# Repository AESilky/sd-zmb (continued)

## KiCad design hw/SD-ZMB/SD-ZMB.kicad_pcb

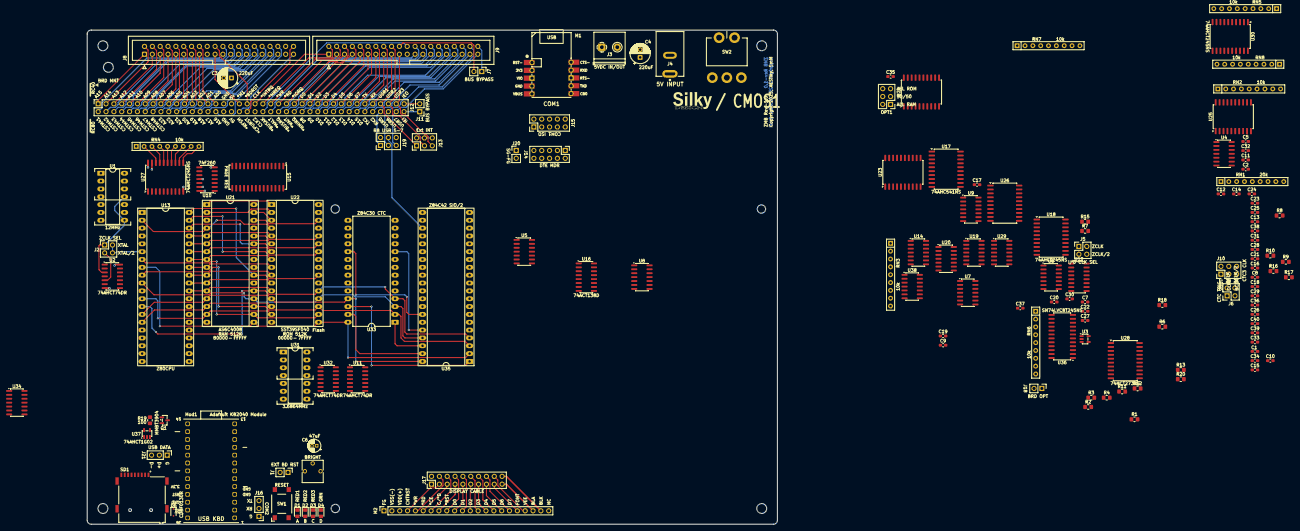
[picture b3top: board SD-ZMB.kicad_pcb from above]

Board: 4 copper layers, 223.5 x 160.0 mm, 147 parts (0 on the bottom side), 263 nets.

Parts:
C1, C2, C5, C7, C8, C9, C10, C11, C12, C13, C14, C15, C16, C17, C18, C19, C20, C21, C22, C23, C24, C25, C26, C27, C28, C29, C30, C31, C32, C33, C34, C35, C36, C37, C38, C39, C40: 0.1uF; C_0603_1608Metric_Pad1.08x0.95mm_HandSolder
C3, C4: 220uF; CP_Radial_D6.3mm_P2.50mm
C6: 47uF; CP_Radial_D4.0mm_P1.50mm
D1, D2, D3: LED RED; LED_0805_2012Metric_Pad1.15x1.40mm_HandSolder
D4: LED GREEN; LED_0805_2012Metric_Pad1.15x1.40mm_HandSolder
D6: CDBF0130R; D_SOD-323F
H1, H2, H3, H4, H8: MountingHole; MountingHole_3.2mm_M3
H5, H6, H7: MountingHole; MountingHole_2.7mm_M2.5
J1, J7, J11, J18, J20: HDR 1x02 Pin; PinHeader_1x02_P2.54mm_Vertical
J2, J5, J6: HDR 02x02; PinHeader_2x02_AB-AES
J3: Screw_Terminal_01x02; AES-TermBlock-2POS-5mm-Horz
J4: BARREL JACK; AES-CUI_PJ-037B
J8, J9: HDR 02x20 PIN (Ribbon Socket); IDC-Header_2x20_P2.54mm_Vertical
J10, J19: Conn_02x03; PinHeader_2x03_AB-AES
J12: SOCKET 02x40 (BRD-CONN); RC80-BUS-BPMB-AES
J13: HDR 02x03 PIN; PinHeader_2x03_AB-AES
J14: CONN 02x05 - DTE_HDR-AES; AES-PinHeader_2x05_DB9-Order
J15: Conn_02x05 HDR; PinHeader_2x05_AB-AES
J16, J21: HDR 1x3 Pin; PinHeader_1x03_P2.54mm_Vertical
J17: HDR 2x10 Pin; PinHeader_2x10_P2.54mm_Vertical
M1: AES-FTDI_FT234XF_USB_UART_Module; AES-FTDI-UMFT234XF
M2: DISPLAY; OLED-Disp-Socket-P2-8BitPI-AES
Mod1: Adafruit KB2040 Module; Adafruit-KB2040-AES
OPT1: HDR 02x03; PinHeader_2x03_AB-AES
Q1: MMBT3904; SOT-23
R1, R2, R3, R4: 510; R_0805_2012Metric_Pad1.20x1.40mm_HandSolder
R6: 10k; R_0805_2012Metric_Pad1.20x1.40mm_HandSolder
R7, R8, R9, R10, R11, R12, R13, R15, R16, R17, R18: 22; R_0805_2012Metric_Pad1.20x1.40mm_HandSolder
R19: 100; R_0805_2012Metric_Pad1.20x1.40mm_HandSolder
R20: 180; R_0805_2012Metric_Pad1.20x1.40mm_HandSolder
RN1: 20k; R_Array_SIP9
RN2, RN3, RN4, RN5, RN6, RN7, RN8: 10k; R_Array_SIP9
RV1: 10k; Pot-Molence-Amazon-PCB-AES
SD1: MicroSD-Socket; AES-SDCard-GCT_MEM2075-00-140-01-A
SW1: SW_Push; AES-SW_PUSH_SMD_1P1T_NO_6x6mm
SW2: SW Toggle PCB; SW-SPDT-PCB-TGL-RA-AES
U1: 12MHz; DIP-14_W7.62mm_LongPads
U2, U11, U32: 74AHCT74DR; SOIC-14_3.9x8.7mm_P1.27mm
U3: MIC2775; SOT-23-5
U4, U5: 74AHCT08; SOIC-14_3.9x8.7mm_P1.27mm
U6, U8: 74AHCT00; SOIC-14_3.9x8.7mm_P1.27mm
U7: 74AHCT02; SOIC-14_3.9x8.7mm_P1.27mm
U9, U38: 74AHCT32; SOIC-14_3.9x8.7mm_P1.27mm
U10: 74F260; SOIC-14_3.9x8.7mm_P1.27mm
U12, U16: 74ACT138D; SOIC-16_3.9x9.9mm_P1.27mm
U13: Z80CPU; DIP-40_W15.24mm_Socket_LongPads
U14, U29: 74F27; SOIC-14_3.9x8.7mm_P1.27mm
U15: SRAM 8K/32K; SOJ-28_7.62x18.415mm_P1.27mm
U17: 74AHC541NS; SOIC-20W_7.5x12.8mm_P1.27mm
U18, U25, U26, U27, U30: 74AHCT245NS; SOIC-20W_7.5x12.8mm_P1.27mm
U19, U34: 74AHCT10; SOIC-14_3.9x8.7mm_P1.27mm
U20: 74AC11; SOIC-14_3.9x8.7mm_P1.27mm
U21: AS6C4008; DIP-32_W15.24mm_Socket_LongPads
U22: SST39SF040; DIP-32_W15.24mm_Socket_LongPads
U23, U24: 74AHCT244NS; SOIC-20W_7.5x12.8mm_P1.27mm
U28: 74HCT273NS; SOIC-20W_7.5x12.8mm_P1.27mm
U31: 3.6864MHz; DIP-14_W7.62mm_LongPads
U33: Z84C30 CTC; DIP-28_W15.24mm_LongPads
U35: Z84C42 SIO/2; DIP-40_W15.24mm_Socket_LongPads
U36: SN74LVC8T245NS; SO-24_5.3x15mm_P1.27mm
U37: 74AHCT1G02; SOT-23-5

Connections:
+3.3V: Mod1.22 (3.3V), SD1.4 (VDD), U36.23 (V_{CCB}), U36.24 (V_{CCB})
+5V: C1.2, C2.2, C3.1, C4.1, C5.1, C6.1, C7.2, C8.2, C9.2, C10.2, C11.2, C12.2, C13.2, C14.2, C15.2, C16.2, C17.2, C18.2, C19.2, C20.2, C21.2, C22.2, C23.2, C24.2, C25.2, C26.2, C27.2, C28.2, C29.2, C30.2, C31.2, C32.2, C33.2, C34.2, C35.2, C36.2, C37.2, C38.2, C39.2, C40.2, D6.2 (A), J3.2, J8.18, J8.38, J12.18 (5V), J12.58 (5V), J17.2, J17.19, M2.3 (PWR), M2.20 (BLA/BLK), R1.2, R2.2, R3.2, R6.2, RN2.1 (common), RN3.1 (common), RN4.1 (common), RN5.1 (common), RN6.1 (common), RN7.1 (common), RN8.1 (common), SW2.3 (C), U1.1 (EN), U1.14 (PWR), U2.14 (VCC), U3.5 (VDD), U4.14 (VCC), U5.14 (VCC), U6.14 (VCC), U7.14 (VCC), U8.14 (VCC), U9.14 (VCC), U10.14 (VCC), U11.14 (VCC), U12.16 (VCC), U13.11 (V_{CC}), U14.14 (VCC), U15.28 (V_{CC}), U16.16 (VCC), U17.20 (VCC), U18.20 (VCC), U19.14 (VCC), U20.14 (VCC), U21.32 (VCC), U22.32 (VCC), U23.20 (VCC), U24.20 (VCC), U25.20 (VCC), U26.20 (VCC), U27.20 (VCC), U28.20 (VCC), U29.14 (VCC), U30.20 (VCC), U31.1 (EN), U31.14 (PWR), U32.14 (VCC), U33.24 (VCC), U34.14 (VCC), U35.9 (VCC), U36.1 (V_{CCA}), U37.5 (VCC), U38.14 (VCC)
/ExpIFC-SIOCTC/B0IEO: J7.2, J9.20, U4.12
/ExpIFC-SIOCTC/B1IEI: J11.1, J12.80 (IEI), U4.11
/ExpIFC-SIOCTC/B1IEO: J11.2, J12.40 (IEO)
/ExpIFC-SIOCTC/BA00: J8.16, J12.16 (A0)
/ExpIFC-SIOCTC/BA01: J8.15, J12.15 (A1)
/ExpIFC-SIOCTC/BA02: J8.14, J12.14 (A2)
/ExpIFC-SIOCTC/BA03: J8.13, J12.13 (A3)
/ExpIFC-SIOCTC/BA04: J8.12, J12.12 (A4)
/ExpIFC-SIOCTC/BA05: J8.11, J12.11 (A5)
/ExpIFC-SIOCTC/BA06: J8.10, J12.10 (A6)
/ExpIFC-SIOCTC/BA07: J8.9, J12.9 (A7)
/ExpIFC-SIOCTC/BA08: J8.8, J12.8 (A8)
/ExpIFC-SIOCTC/BA09: J8.7, J12.7 (A9)
/ExpIFC-SIOCTC/BLB: J17.3, M2.4 (V0), RV1.2
/ExpIFC-SIOCTC/BLPWR: J17.18, M2.19 (VEE/BLA), R20.1
/ExpIFC-SIOCTC/CHA_CLK: U33.7 (ZC/TO0), U35.13 (~RxCA), U35.14 (~TxCA)
/ExpIFC-SIOCTC/CHB_CLK: U33.8 (ZC/TO1), U35.27 (~TxCB), U35.28 (~RxCB)
/ExpIFC-SIOCTC/CSTM41: J8.21, J12.41 (CSTM41)
/ExpIFC-SIOCTC/CSTM42: J8.22, J12.42 (CSTM42)
/ExpIFC-SIOCTC/CSTM43: J8.23, J12.43 (CSTM43)
/ExpIFC-SIOCTC/CSTM44: J8.24, J12.44 (CSTM44)
/ExpIFC-SIOCTC/CSTM45: J8.25, J12.45 (CSTM45)
/ExpIFC-SIOCTC/CSTM46: J8.26, J12.46 (CSTM46)
/ExpIFC-SIOCTC/CSTM47: J8.27, J12.47 (CSTM47)
/ExpIFC-SIOCTC/CSTM48: J8.28, J12.48 (CSTM48)
/ExpIFC-SIOCTC/CTC2_OUT: J10.a1, U33.9 (ZC/TO2)
/ExpIFC-SIOCTC/CTC3_CLK: J10.b1, J10.b2, J10.b3, U33.20 (CLK/TRG3)
/ExpIFC-SIOCTC/CTCIEO: U5.13, U33.11 (IEO), U34.2
/ExpIFC-SIOCTC/CTC_CLK2: J6.b1, J6.b2, J10.a2, U33.21 (CLK/TRG2)
/ExpIFC-SIOCTC/CTS_A: J14.8 (CTS), J15.a3, R16.2
/ExpIFC-SIOCTC/DCD_A: J14.1 (DCD), J15.a5, R17.2
/ExpIFC-SIOCTC/DTR_A: J14.4 (DTR), R10.2
/ExpIFC-SIOCTC/EXTIRQ-: J13.b1, J13.b2, J13.b3, R6.1, U35.22 (~DCDB)
/ExpIFC-SIOCTC/FONT_BL: J17.17, M2.18 (FONT), R13.2
/ExpIFC-SIOCTC/IOCLK: J5.b1, J5.b2, J9.21, J12.61 (CLK2), U33.15 (CLK), U35.20 (CLK)
/ExpIFC-SIOCTC/LCLIA-: J7.1, J9.40, U4.13, U5.11
/ExpIFC-SIOCTC/MHZ3_7: J6.a1, J10.a3, U31.8 (O), U31.11 (O), U32.3 (C), U33.22 (CLK/TRG1), U33.23 (CLK/TRG0)
/ExpIFC-SIOCTC/NC_D08: J9.27, J12.67 (D8)
/ExpIFC-SIOCTC/NC_D09: J9.28, J12.68 (D9)
/ExpIFC-SIOCTC/NC_D10: J9.29, J12.69 (D10)
/ExpIFC-SIOCTC/NC_D11: J9.30, J12.70 (D11)
/ExpIFC-SIOCTC/NC_D12: J9.31, J12.71 (D12)
/ExpIFC-SIOCTC/NC_D13: J9.32, J12.72 (D13)
/ExpIFC-SIOCTC/NC_D14: J9.33, J12.73 (D14)
/ExpIFC-SIOCTC/NC_D15: J9.34, J12.74 (D15)
/ExpIFC-SIOCTC/RI_A: J14.9 (RI), R8.2
/ExpIFC-SIOCTC/RTS_A: J14.7 (RTS), J15.a4, R9.2
/ExpIFC-SIOCTC/RTS_B: J19.b3, R18.2
/ExpIFC-SIOCTC/RXD_A: J9.16, J12.36 (RX), J14.2 (RXD), J15.a1, R7.2
/ExpIFC-SIOCTC/RXD_B: J9.36, J12.76 (RX2), J16.2, Mod1.2 (GPIO0_UTX0), R11.2
/ExpIFC-SIOCTC/SDCS-: Mod1.14 (GPIO10_PWM5A), SD1.2 (DAT3/CD)
/ExpIFC-SIOCTC/SIOIEO: U5.12, U33.13 (IEI), U34.1, U35.7 (IEO)
/ExpIFC-SIOCTC/SPICK: Mod1.17 (GPIO18_SCK0), SD1.5 (CLK)
/ExpIFC-SIOCTC/SPIMI: Mod1.16 (GPIO20_MISO0), SD1.7 (DAT0)
/ExpIFC-SIOCTC/SPIMO: Mod1.15 (GPIO19_MOSI0), SD1.3 (CMD)
/ExpIFC-SIOCTC/TXD_A: J9.15, J12.35 (TX), J14.3 (TXD), J15.a2, R15.2
/ExpIFC-SIOCTC/TXD_B: J9.35, J12.75 (TX2), J16.3, Mod1.3 (GPIO1_URX0), R12.2
/ExpIFC-SIOCTC/UHPWR5: D6.1 (K), Mod1.25 (5V_RAW)
/ExpIFC-SIOCTC/USBD+: J21.2, Mod1.1 (D+)
/ExpIFC-SIOCTC/USBD-: J21.3, Mod1.26 (D-)
/ExpIFC-SIOCTC/USR1: J9.17, J12.37 (User1), J13.a1
/ExpIFC-SIOCTC/USR2: J9.18, J12.38 (User2), J13.a2
/ExpIFC-SIOCTC/USR3: J9.19, J12.39 (User3), J13.a3
/ExpIFC-SIOCTC/V3D0: Mod1.6 (GPIO2_SDA1), U36.21 (B1)
/ExpIFC-SIOCTC/V3D1: Mod1.7 (GPIO3_SCL1), U36.20 (B2)
/ExpIFC-SIOCTC/V3D2: Mod1.8 (GPIO4_UTX1), U36.19 (B3)
/ExpIFC-SIOCTC/V3D3: Mod1.9 (GPIO5_URX1), U36.18 (B4)
/ExpIFC-SIOCTC/V3D4: Mod1.10 (GPIO6_PWM3A), U36.17 (B5)
/ExpIFC-SIOCTC/V3D5: Mod1.11 (GPIO7_PWM3B), U36.16 (B6)
/ExpIFC-SIOCTC/V3D6: Mod1.12 (GPIO8_PWM4A), U36.15 (B7)
/ExpIFC-SIOCTC/V3D7: Mod1.13 (GPIO9_PWM4B), U36.14 (B8)
/ExpIFC-SIOCTC/WAIT: R19.1, U37.4
/ExpIFC-SIOCTC/WAITRQ-: Mod1.18 (GPIO26_A0), U37.1
/LOGIC_PWR_SPARES/VPU2: U32.10 (~S), U32.13 (~R)
/MainBoard-CPU_Decode/BA00: RN2.2 (R1), U25.18 (B0)
/MainBoard-CPU_Decode/BA01: RN2.3 (R2), U25.17 (B1)
/MainBoard-CPU_Decode/BA02: RN2.4 (R3), U25.16 (B2)
/MainBoard-CPU_Decode/BA03: RN2.5 (R4), U25.15 (B3)
/MainBoard-CPU_Decode/BA04: RN2.6 (R5), U25.14 (B4)
/MainBoard-CPU_Decode/BA05: RN2.7 (R6), U25.13 (B5)
/MainBoard-CPU_Decode/BA06: RN2.8 (R7), U25.12 (B6)
/MainBoard-CPU_Decode/BA07: RN2.9 (R8), U25.11 (B7)
/MainBoard-CPU_Decode/BA08: RN3.2 (R1), U26.18 (B0)
/MainBoard-CPU_Decode/BA09: RN3.3 (R2), U26.17 (B1)
/MainBoard-CPU_Decode/BAtoMHA-: U4.9, U9.8, U23.1 (~OEa)
/MainBoard-CPU_Decode/BAtoZA-: U4.8, U25.1 (A>B), U26.1 (A>B), U27.1 (A>B)
/MainBoard-CPU_Decode/BAtoZAH-: U4.10, U8.6, U23.19 (~OEb)
/MainBoard-CPU_Decode/BDCTLWR-: U19.8, U28.11 (Cp)
/MainBoard-CPU_Decode/BDCTRL-: U12.10 (~Y5), U14.10
/MainBoard-CPU_Decode/BDTOZD-: U29.8, U30.1 (A>B)
/MainBoard-CPU_Decode/BMBTOZ: U29.6, U29.11
/MainBoard-CPU_Decode/BUSIO-: U5.10, U9.6
/MainBoard-CPU_Decode/BUSMEM-: U5.9, U9.12, U19.6
/MainBoard-CPU_Decode/FLASHRD-: U16.15 (~Y0), U22.24 (OE#)
/MainBoard-CPU_Decode/FLASHWR-: U16.13 (~Y2), U22.31 (PGM#)
/MainBoard-CPU_Decode/LCLIO: U7.9, U8.5, U9.4, U10.5, U14.4
/MainBoard-CPU_Decode/LCLMEM: U7.8, U20.12
/MainBoard-CPU_Decode/LCLMEM-: U9.9, U19.12, U21.22 (CE#), U22.22 (CE#)
/MainBoard-CPU_Decode/LOW1MEG: U10.6, U14.1, U14.2, U14.13, U16.6 (E2), U19.13, U20.13
/MainBoard-CPU_Decode/LOW1MEG-: U14.12, U19.5
/MainBoard-CPU_Decode/MHA13: U15.11 (I/O_{1}), U17.18 (Y0), U18.2 (A0), U21.28 (A13), U22.28 (A13), U23.18 (O0a), U24.18 (O0a)
/MainBoard-CPU_Decode/MHA14: U15.12 (I/O_{2}), U17.17 (Y1), U18.3 (A1), U21.3 (A14), U22.29 (A14), U23.16 (O1a), U24.16 (O1a)
/MainBoard-CPU_Decode/MHA15: U15.13 (I/O_{3}), U17.16 (Y2), U18.4 (A2), U21.31 (A15), U22.3 (A15), U23.14 (O2a), U24.14 (O2a)
/MainBoard-CPU_Decode/MHA16: U15.15 (I/O_{4}), U17.15 (Y3), U18.5 (A3), U21.2 (A16), U22.2 (A16), U27.2 (A0)
/MainBoard-CPU_Decode/MHA17: U15.16 (I/O_{5}), U17.14 (Y4), U18.6 (A4), U21.30 (A17), U22.30 (A17), U27.3 (A1)
/MainBoard-CPU_Decode/MHA18: U15.17 (I/O_{6}), U17.13 (Y5), U18.7 (A5), U21.1 (A18), U22.1 (A18), U27.4 (A2)
/MainBoard-CPU_Decode/MHA19: U15.18 (I/O_{7}), U16.3 (A2), U17.12 (Y6), U18.8 (A6), U27.5 (A3)
/MainBoard-CPU_Decode/MHA20: U10.4, U15.19 (I/O_{8}), U17.11 (Y7), U18.9 (A7), U27.6 (A4)
/MainBoard-CPU_Decode/MHA21: RN1.6 (R5), U10.8, U27.7 (A5)
/MainBoard-CPU_Decode/MHA22: RN1.7 (R6), U10.9, U27.8 (A6)
/MainBoard-CPU_Decode/MHA23: RN1.8 (R7), U10.10, U27.9 (A7)
/MainBoard-CPU_Decode/MHAtoBA-: U9.11, U24.1 (~OEa)
/MainBoard-CPU_Decode/MHZ12: J2.a1, U1.8 (O), U1.11 (O), U2.3 (C)
/MainBoard-CPU_Decode/NMIEN: U8.1, U8.2, U28.19 (Q7)
/MainBoard-CPU_Decode/PDA16: RN1.2 (R1), U17.5 (A3)
/MainBoard-CPU_Decode/PDA17: RN1.3 (R2), U17.6 (A4)
/MainBoard-CPU_Decode/PDA18: RN1.4 (R3), U17.7 (A5)
/MainBoard-CPU_Decode/PDA20: RN1.5 (R4), U17.9 (A7)
/MainBoard-CPU_Decode/PGENWR-: U2.11 (C), U11.4 (~S), U12.7 (~Y7)
/MainBoard-CPU_Decode/PGINGEN: U2.9 (Q), U6.4
/MainBoard-CPU_Decode/PGRGRD-: U5.5, U38.3
/MainBoard-CPU_Decode/PGRGSEL-: U8.9, U12.9 (~Y6), U18.19 (~OE), U38.2, U38.4
/MainBoard-CPU_Decode/PGRGWR-: U15.27 (~WE), U18.1 (A>B), U38.6
/MainBoard-CPU_Decode/PRA3: U4.6, U15.7 (A_{3})
/MainBoard-CPU_Decode/PROE-: U5.6, U15.22 (~OE)
/MainBoard-CPU_Decode/RA55RO: OPT1.b1, OPT1.b2, OPT1.b3, U17.8 (A6)
/MainBoard-CPU_Decode/SRAMRD-: U16.9 (~Y6), U21.24 (OE#)
/MainBoard-CPU_Decode/SRAMWR-: U16.11 (~Y4), U21.29 (WE#)
/MainBoard-CPU_Decode/ZAtHoBA-: U14.6, U24.19 (~OEb)
/MainBoard-CPU_Decode/ZDBDEN-: U30.19 (~OE), U34.8
/MainBoard-CPU_Decode/ZMASTER: U5.3, U6.5, U8.12, U9.10, U29.3
/MainBoard-CPU_Decode/ZMASTER-: U6.3, U7.12, U8.4, U9.13, U14.3, U29.1
/MainBoard-CPU_Decode/ZMBTOZ: U29.10, U29.12
/MainBoard-CPU_Decode/ZMNIO-: U5.4, U8.11
/MainBoard-CPU_Decode/ZPGPRS: U8.8, U17.1 (~G1), U17.19 (~G2)
/MainBoard-CPU_Decode/ZRST: U6.11, U11.3 (C)
BA10: J8.6, J12.6 (A10), RN3.4 (R3), U26.16 (B2)
BA11: J8.5, J12.5 (A11), RN3.5 (R4), U26.15 (B3)
BA12: J8.4, J12.4 (A12), RN3.6 (R5), U23.8 (I3a), U23.11 (I0b), U24.8 (I3a), U24.11 (I0b)
BA13: J8.3, J12.3 (A13), RN3.7 (R6), U23.2 (I0a), U23.17 (I3b), U24.2 (I0a), U24.17 (I3b)
BA14: J8.2, J12.2 (A14), RN3.8 (R7), U23.4 (I1a), U23.15 (I2b), U24.4 (I1a), U24.15 (I2b)
BA15: J8.1, J12.1 (A15), RN3.9 (R8), U23.6 (I2a), U23.13 (I1b), U24.6 (I2a), U24.13 (I1b)
BA16: J8.36, J12.56 (A16), RN4.2 (R1), U27.18 (B0)
BA17: J8.35, J12.55 (A17), RN4.3 (R2), U27.17 (B1)
BA18: J8.34, J12.54 (A18), RN4.4 (R3), U27.16 (B2)
BA19: J8.33, J12.53 (A19), RN4.5 (R4), U27.15 (B3)
BA20: J8.32, J12.52 (A20), RN4.6 (R5), U27.14 (B4)
BA21: J8.31, J12.51 (A21), RN4.7 (R6), U27.13 (B5)
BA22: J8.30, J12.50 (A22), RN4.8 (R7), U27.12 (B6)
BA23: J8.29, J12.49 (A23), RN4.9 (R8), U27.11 (B7)
BD0: J9.7, J12.27 (D0), RN8.2 (R1), U30.18 (B0)
BD1: J9.8, J12.28 (D1), RN8.3 (R2), U30.17 (B1)
BD2: J9.9, J12.29 (D2), RN8.4 (R3), U30.16 (B2)
BD3: J9.10, J12.30 (D3), RN8.5 (R4), U30.15 (B3)
BD4: J9.11, J12.31 (D4), RN8.6 (R5), U30.14 (B4)
BD5: J9.12, J12.32 (D5), RN8.7 (R6), U30.13 (B5)
BD6: J9.13, J12.33 (D6), RN8.8 (R7), U30.12 (B6)
BD7: J9.14, J12.34 (D7), RN8.9 (R8), U30.11 (B7)
BD_OPT1-: J18.2, J19.b2, RN6.7 (R6), U35.23 (~CTSB)
BIORQ-: J9.6, J12.26 (~IORQ), RN6.5 (R4), U26.11 (B7)
BMREQ-: J9.3, J12.23 (~MREQ), RN6.4 (R3), U26.12 (B6)
BRD-: J9.5, J12.25 (~RD), RN6.2 (R1), U26.14 (B4)
BRDRST-: J8.20, J12.20 (~RESET), J17.8, M1.1 (RESET-), M2.9 (~RST), Mod1.23 (RESET), U2.1 (~R), U3.1 (~RST), U4.1, U11.13 (~R), U28.1 (~Mr), U33.17 (~RESET), U35.21 (~RESET)
BUSIA-: U7.11, U34.12
BWR-: J9.4, J12.24 (~WR), RN6.3 (R2), U26.13 (B5)
CPURST-: J8.40, J12.60 (~CPURST), RN7.2 (R1), U4.2
CTC_SEL-: U12.14 (~Y1), U33.16 (~CE)
DISPSEL-: J17.6, M2.7 (~CE), U12.12 (~Y3)
Earth: J14.10 (CHGND), J20.2
GND: C1.1, C2.1, C3.2, C4.2, C5.2, C6.2, C7.1, C8.1, C9.1, C10.1, C11.1, C12.1, C13.1, C14.1, C15.1, C16.1, C17.1, C18.1, C19.1, C20.1, C21.1, C22.1, C23.1, C24.1, C25.1, C26.1, C27.1, C28.1, C29.1, C30.1, C31.1, C32.1, C33.1, C34.1, C35.1, C36.1, C37.1, C38.1, C39.1, C40.1, J1.1, J3.1, J4.2, J8.17, J8.37, J12.17 (GND), J12.57 (GND), J14.5 (GND), J16.1, J17.1, J17.20, J18.1, J20.1, J21.1, M1.4 (GND), M2.1 (F_GND), M2.2 (VSS), M2.21 (BLK/NC), Mod1.4 (GND), Mod1.5 (GND), Mod1.24 (GND), OPT1.a3, Q1.2 (E), R4.2, RN1.1 (common), RV1.1, SD1.6 (VSS), SD1.10 (SHIELD), SW1.2, U1.4 (G), U1.7 (G), U2.7 (GND), U3.2 (GND), U4.7 (GND), U5.7 (GND), U6.7 (GND), U7.7 (GND), U8.7 (GND), U9.7 (GND), U10.7 (GND), U10.11, U10.13, U11.2 (D), U11.7 (GND), U12.8 (GND), U13.29 (GND), U14.7 (GND), U14.11, U15.1 (A14/NC), U15.2 (A_{12}), U15.3 (A_{7}), U15.4 (A_{6}), U15.5 (A_{5}), U15.6 (A_{4}), U15.14 (GND), U15.20 (~CE_{1}), U15.21 (A_{10}), U15.23 (A_{11}), U15.24 (A_{9}), U15.25 (A_{8}), U16.5 (~E1), U16.8 (GND), U17.10 (GND), U18.10 (GND), U19.7 (GND), U20.3, U20.4, U20.5, U20.7 (GND), U20.9, U20.10, U20.11, U21.16 (VSS), U22.16 (GND), U23.10 (GND), U24.10 (GND), U25.10 (GND), U25.19 (~OE), U26.10 (GND), U26.19 (~OE), U27.10 (GND), U27.19 (~OE), U28.10 (GND), U29.7 (GND), U30.10 (GND), U31.4 (G), U31.7 (G), U32.7 (GND), U33.5 (GND), U34.7 (GND), U35.31 (GND), U36.11 (GND), U36.12 (GND), U36.13 (GND), U37.3 (GND), U38.7 (GND), U38.9, U38.10, U38.12, U38.13
INTACK: U7.1, U34.13
NMIREQ-: RN7.4 (R3), U9.1
unnamed: D1.2 (A), R1.1
unnamed: D1.1 (K), U28.2 (Q0)
unnamed: D2.2 (A), R2.1
unnamed: D2.1 (K), U28.5 (Q1)
unnamed: D3.2 (A), R3.1
unnamed: D3.1 (K), U28.6 (Q2)
unnamed: D4.2 (A), U28.9 (Q3)
unnamed: D4.1 (K), R4.1
unnamed: J1.2, SW1.1, U3.4 (~MR)
unnamed: J2.a2, U2.5 (Q)
unnamed: J5.a2, U11.9 (Q)
unnamed: J6.a2, U32.5 (Q)
unnamed: J15.b1, M1.7 (TXD(O))
unnamed: J15.b2, M1.9 (RXD(I))
unnamed: J15.b3, M1.8 (RTS-(O))
unnamed: J15.b4, M1.10 (CTS-(I))
unnamed: J15.b5, M1.6 (CB0)
unnamed: Q1.1 (B), R19.2
unnamed: R20.2, RV1.3
unnamed: J4.1, SW2.2 (B)
unnamed: U2.2 (D), U2.6 (~Q)
unnamed: U6.6, U8.10
unnamed: U8.3, U9.2
unnamed: U2.13 (~R), U11.5 (Q)
unnamed: U11.8 (~Q), U11.12 (D)
unnamed: U7.4, U12.6 (E2)
unnamed: U6.8, U10.1, U12.4 (~E0)
unnamed: U14.8, U19.9, U19.10, U19.11
unnamed: U7.10, U29.5
unnamed: U7.13, U29.9
unnamed: U5.8, U29.13
unnamed: U32.2 (D), U32.6 (~Q)
unnamed: U34.6, U34.10, U34.11
unnamed: R7.1, U35.12 (RxDA)
unnamed: R11.1, U35.29 (RxDB)
unnamed: R15.1, U35.15 (TxDA)
unnamed: R12.1, U35.26 (TxDB)
unnamed: R16.1, U35.18 (~CTSA)
unnamed: R17.1, U35.19 (~DCDA)
unnamed: R10.1, U35.16 (~DTRA)
unnamed: R13.1, U35.25 (~DTRB)
unnamed: R9.1, U35.17 (~RTSA)
unnamed: R18.1, U35.24 (~RTSB)
unnamed: R8.1, U35.11 (~SYNCA)
SIO_SEL-: U12.15 (~Y0), U35.35 (~CE)
USBSDSEL-: Mod1.19 (GPIO27_A1), U12.13 (~Y2), U36.22 (~OE), U37.2
USR5: J9.37, J12.77 (User5), J19.a1, U28.12 (Q4)
USR6: J9.38, J12.78 (User6), J19.a2, U28.15 (Q5)
USR7: J9.39, J12.79 (User7), J19.a3, U28.16 (Q6)
VPU1: RN6.8 (R7), U11.10 (~S), U32.1 (~R), U32.4 (~S)
VPU2: OPT1.a1, RN6.9 (R8), U2.4 (~S), U2.10 (~S), U11.1 (~R), U15.26 (A13/CE_{2}), U35.6 (IEI)
ZA0: J17.7, M2.8 (C/~D), Mod1.21 (GPIO29_A3), U4.4, U13.30 (A_{0}), U21.12 (A0), U22.12 (A0), U25.2 (A0), U33.18 (CS0), U35.33 (C/~D)
ZA1: U13.31 (A_{1}), U21.11 (A1), U22.11 (A1), U25.3 (A1), U33.19 (CS1), U35.34 (B/~A)
ZA2: U7.5, U10.2, U13.32 (A_{2}), U21.10 (A2), U22.10 (A2), U25.4 (A2)
ZA3: U12.1 (A0), U13.33 (A_{3}), U21.9 (A3), U22.9 (A3), U25.5 (A3)
ZA4: U12.2 (A1), U13.34 (A_{4}), U21.8 (A4), U22.8 (A4), U25.6 (A4)
ZA5: U12.3 (A2), U13.35 (A_{5}), U21.7 (A5), U22.7 (A5), U25.7 (A5)
ZA6: U7.6, U10.3, U13.36 (A_{6}), U21.6 (A6), U22.6 (A6), U25.8 (A6)
ZA7: U6.9, U13.37 (A_{7}), U21.5 (A7), U22.5 (A7), U25.9 (A7)
ZA8: U13.38 (A_{8}), U21.27 (A8), U22.27 (A8), U26.2 (A0)
ZA9: U13.39 (A_{9}), U21.26 (A9), U22.26 (A9), U26.3 (A1)
ZA10: U13.40 (A_{10}), U21.23 (A10), U22.23 (A10), U26.4 (A2)
ZA11: U13.1 (A_{11}), U21.25 (A11), U22.25 (A11), U26.5 (A3)
ZA12: U13.2 (A_{12}), U21.4 (A12), U22.4 (A12), U23.9 (O0b), U23.12 (O3a), U24.9 (O0b), U24.12 (O3a)
ZA13: U13.3 (A_{13}), U15.10 (A_{0}), U17.2 (A0), U23.7 (O1b), U24.7 (O1b)
ZA14: U13.4 (A_{14}), U15.9 (A_{1}), U17.3 (A1), U23.5 (O2b), U24.5 (O2b)
ZA15: OPT1.a2, U13.5 (A_{15}), U15.8 (A_{2}), U17.4 (A2), U23.3 (O3b), U24.3 (O3b)
ZBREQ-: J9.24, J12.64 (~BSREQ), RN6.6 (R5), U13.25 (~BUSREQ)
ZBSAK-: J9.22, J12.62 (~BSACK), U5.1, U6.1, U13.23 (~BUSACK)
ZCLK: J2.b1, J2.b2, J5.a1, J9.1, J12.21 (CLK), U11.11 (C), U13.6 (CLK)
ZD0: J17.9, M2.10 (D0), RN5.2 (R1), U2.12 (D), U13.14 (D_{0}), U18.18 (B0), U21.13 (DQ0), U22.13 (D0), U28.3 (D0), U30.2 (A0), U33.25 (D0), U35.40 (D0), U36.3 (A1)
ZD1: J17.10, M2.11 (D1), RN5.3 (R2), U13.15 (D_{1}), U18.17 (B1), U21.14 (DQ1), U22.14 (D1), U28.4 (D1), U30.3 (A1), U33.26 (D1), U35.1 (D1), U36.4 (A2)
ZD2: J17.11, M2.12 (D2), RN5.4 (R3), U13.12 (D_{2}), U18.16 (B2), U21.15 (DQ2), U22.15 (D2), U28.7 (D2), U30.4 (A2), U33.27 (D2), U35.39 (D2), U36.5 (A3)
ZD3: J17.12, M2.13 (D3), RN5.5 (R4), U13.8 (D_{3}), U18.15 (B3), U21.17 (DQ3), U22.17 (D3), U28.8 (D3), U30.5 (A3), U33.28 (D3), U35.2 (D3), U36.6 (A4)
ZD4: J17.13, M2.14 (D4), RN5.6 (R5), U13.7 (D_{4}), U18.14 (B4), U21.18 (DQ4), U22.18 (D4), U28.13 (D4), U30.6 (A4), U33.1 (D4), U35.38 (D4), U36.7 (A5)
ZD5: J17.14, M2.15 (D5), RN5.7 (R6), U13.9 (D_{5}), U18.13 (B5), U21.19 (DQ5), U22.19 (D5), U28.14 (D5), U30.7 (A5), U33.2 (D5), U35.3 (D5), U36.8 (A6)
ZD6: J17.15, M2.16 (D6), RN5.8 (R7), U13.10 (D_{6}), U18.12 (B6), U21.20 (DQ6), U22.20 (D6), U28.17 (D6), U30.8 (A6), U33.3 (D6), U35.37 (D6), U36.9 (A7)
ZD7: J17.16, M2.17 (D7), RN5.9 (R8), U13.13 (D_{7}), U18.11 (B7), U21.21 (DQ7), U22.21 (D7), U28.18 (D7), U30.9 (A7), U33.4 (D7), U35.4 (D7), U36.10 (A8)
ZHALT-: J9.23, J12.63 (~HALT), U13.18 (~HALT)
ZINT-: J9.2, J12.22 (~INT), RN7.3 (R2), U13.16 (~INT), U33.12 (~INT), U35.5 (~INT)
ZIORQ-: RN7.9 (R8), U4.5, U7.2, U8.13, U9.5, U10.12, U12.5 (~E1), U13.20 (~IORQ), U14.5, U19.1, U19.3, U19.4, U20.1, U20.2, U26.9 (A7), U33.10 (~IORQ), U34.3, U35.36 (~IORQ)
ZM1-: J8.19, J12.19 (~M1), U6.10, U7.3, U13.27 (~M1), U33.14 (~M1), U35.8 (~M1)
ZMREQ-: RN7.8 (R7), U13.19 (~MREQ), U16.4 (~E0), U26.8 (A6), U34.4, U34.5
ZNMI-: J9.26, J12.66 (~NMI), U9.3, U13.17 (~NMI)
ZRD-: J17.5, M2.6 (~RD), Mod1.20 (GPIO28_A2), RN7.6 (R5), U13.21 (~RD), U16.1 (A0), U26.6 (A4), U29.2, U33.6 (~RD), U35.32 (~RD), U36.2 (A>B), U38.1
ZRFSH-: J8.39, J12.59 (~RFSH), U13.28 (~RFSH), U19.2, U34.9
ZRST-: U4.3, U5.2, U6.2, U6.12, U6.13, U13.26 (~RESET)
ZWAIT-: J9.25, J12.65 (~WAIT), Q1.3 (C), RN7.5 (R4), U13.24 (~WAIT)
ZWR-: J17.4, M2.5 (~WR), RN7.7 (R6), U13.22 (~WR), U14.9, U16.2 (A1), U26.7 (A5), U29.4, U38.5

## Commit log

2025-09-21 Initial
2025-09-23 Update gitignore to skip KiCad lock and backup files.
2025-09-28 Change workspace name
2025-09-28 Simplify (reduce functions included)
2025-10-09 HW: PR4 CPU, Memory, page cleaner.
2025-10-09 History: Add PR4
2025-10-10 PR: PR6, 2 addr busses, exp buffered.
2025-10-11 PR7: Review
2025-10-13 PR7.4: checkpoint only
2025-10-13 DBG: PR1.0, ZMB PR7.5, Timing diagrams
2025-11-05 ZMB: Diagrams and start of PCB. DBG: Updated WAIT. DADPT: Display/Cable PCB ordered.
2025-11-24 ZMB: v1.0 Board RFP
2025-11-24 ZMB: v1.0 w/Spares added. RFP
2025-11-25 ZMB gerbers created. OLED display portion updates.
2026-01-05 Revise hardware specifications in README.md
    Updated specifications for the Memory Management Unit and serial ports, added RP2040 module details, and clarified bus control features.
2026-01-08 PCB received
2026-02-07 Prep for ECO-A
2026-02-12 ECO.A: PG Reg A3 incorrect. Change U17B AND to SPR.1A OR
2026-02-23 FW: Minimal boot code, w/disp, diag, ctc, and sio. Link file to gen ROM.
2026-02-24 Intvec table. Makefiles improved.
2026-03-03 ECO.A: MMU PageReg PRA3 s/b 74AHCT32
2026-03-07 ECO-A: Updated schematic plots
2026-03-08 excel recovery file update
2026-03-14 Serial and Paging functional
2026-04-01 Update project title
